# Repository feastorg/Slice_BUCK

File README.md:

# Buck Converter / Analog Signal Generator Slice

Buck Converter / Analog Signal Generator Slice for BREAD.

## Introduction

[Short introduction on the project.]

## Usage

[Explain how to use the project. Include examples and screenshots if applicable.]

## Documentation

Please refer to the [docs](/docs) for more info.

---

<div align="center">
  
</div>

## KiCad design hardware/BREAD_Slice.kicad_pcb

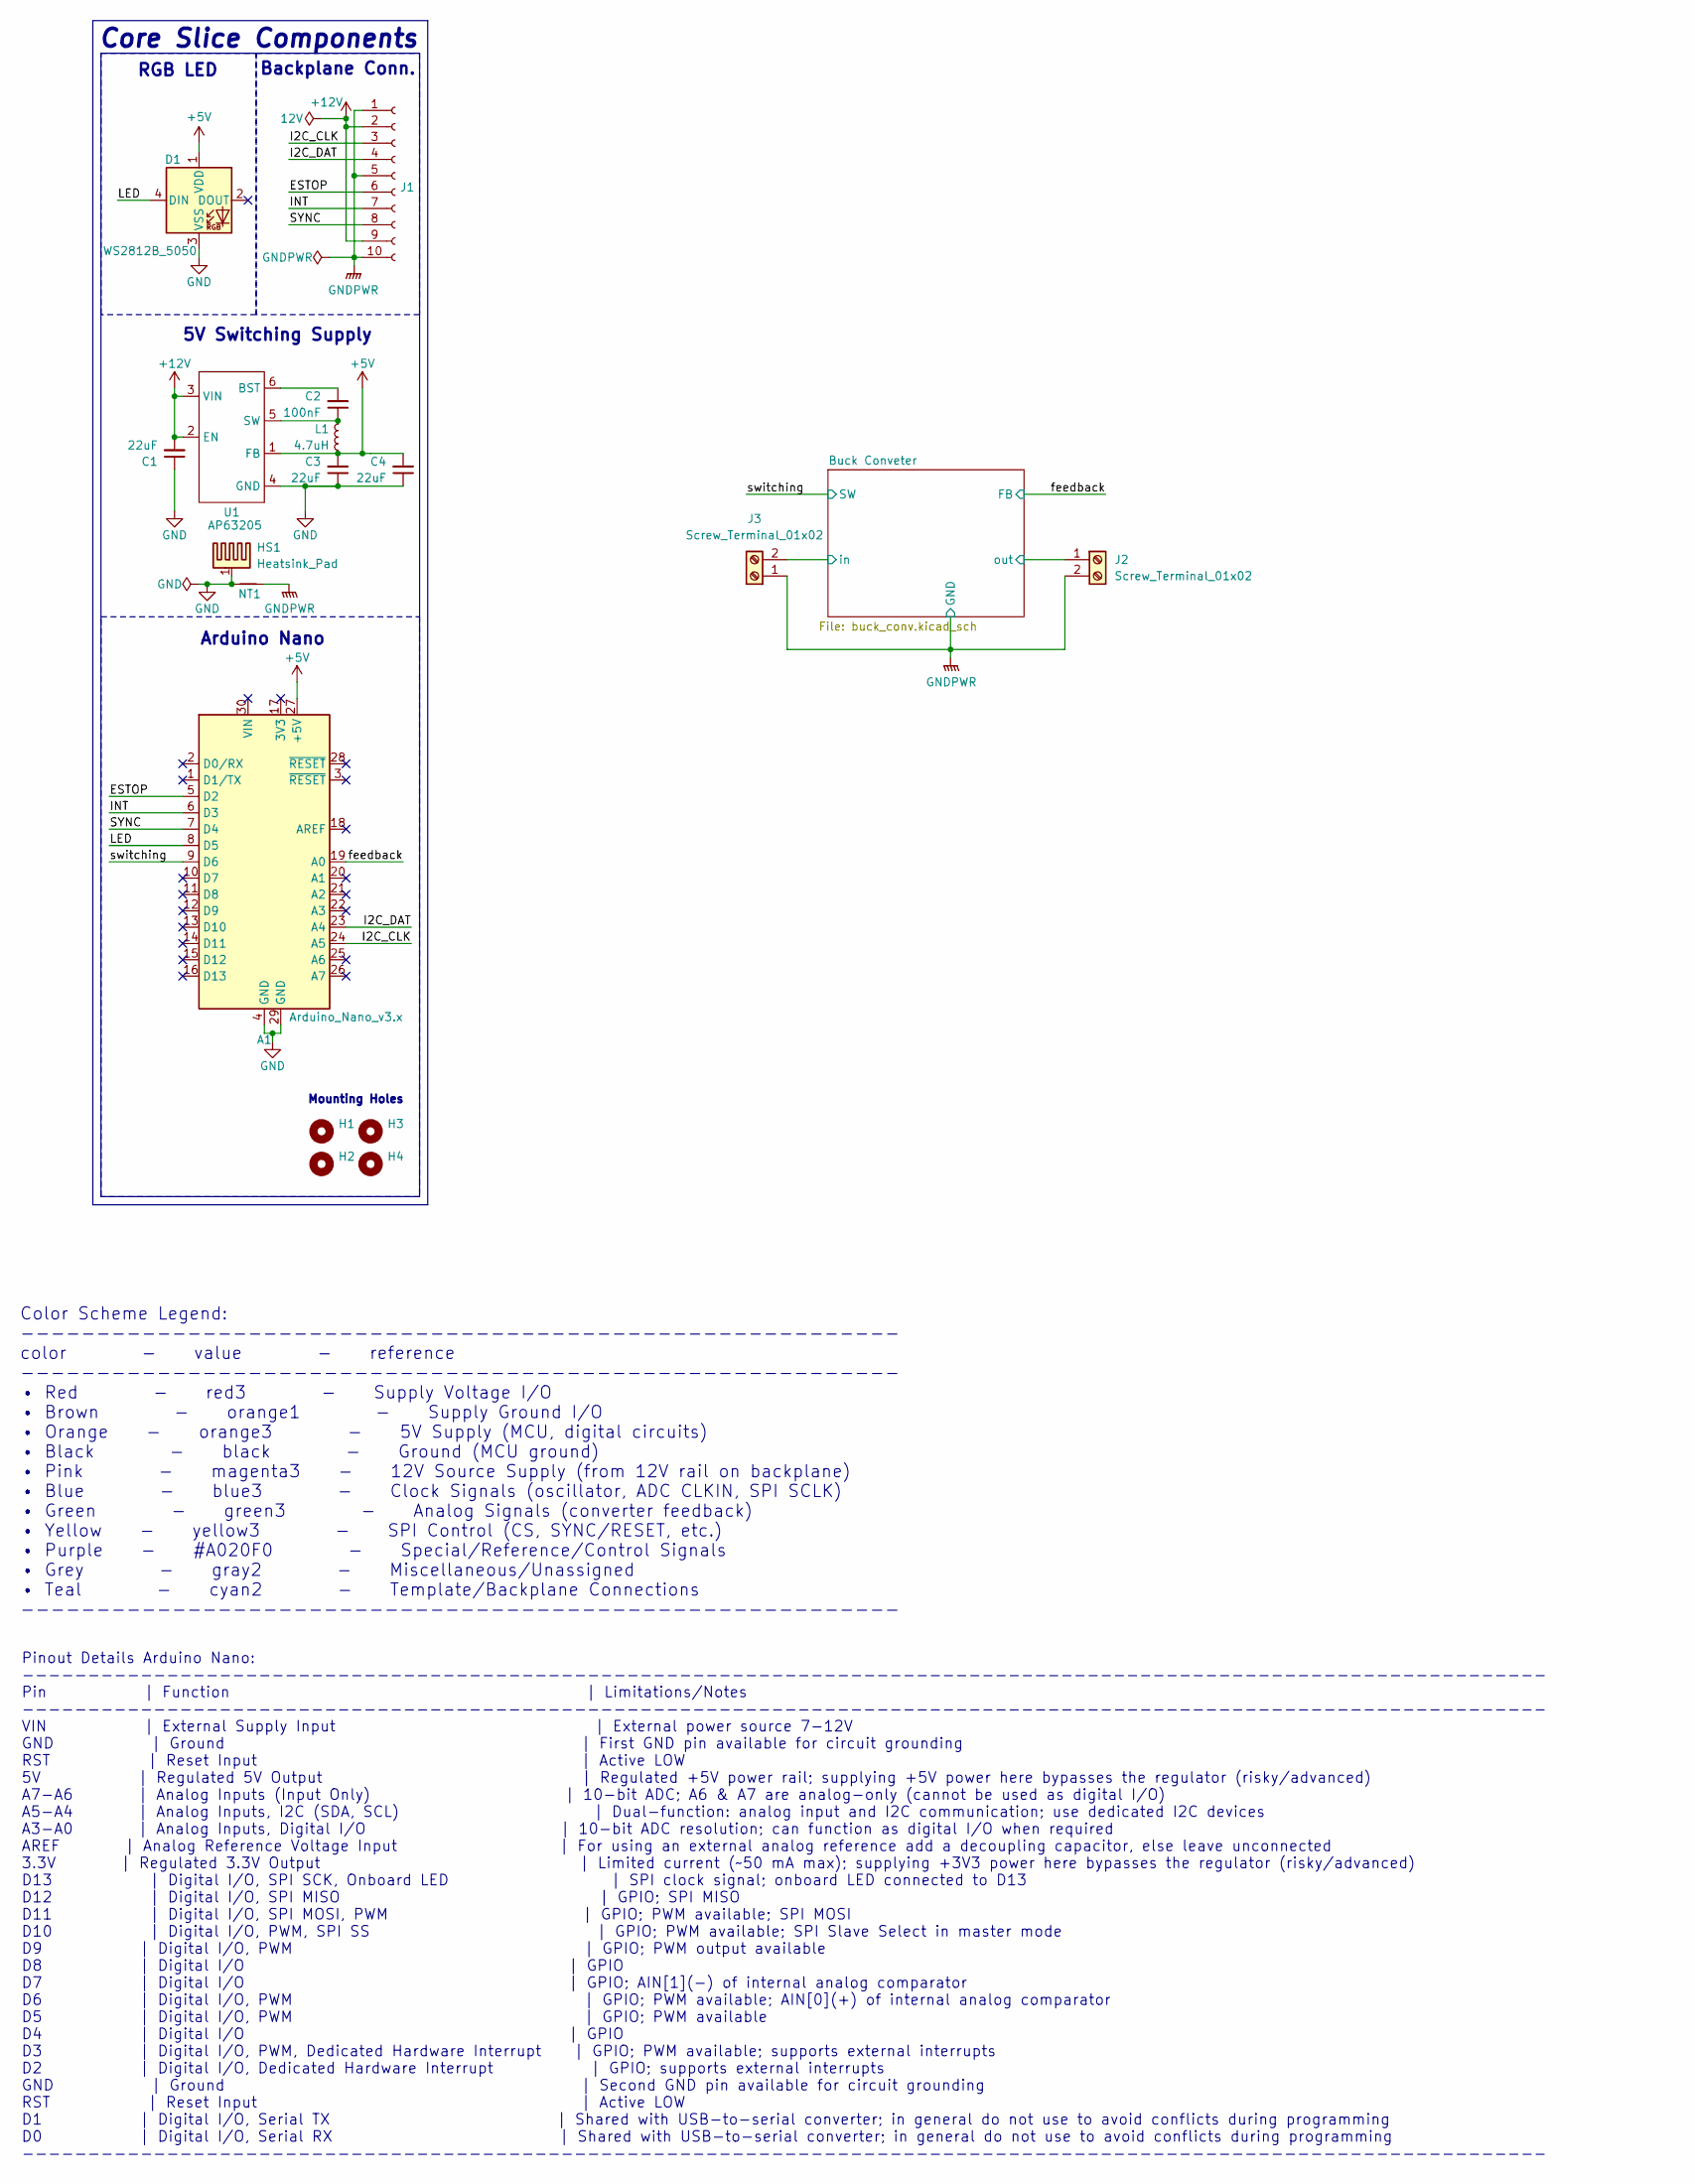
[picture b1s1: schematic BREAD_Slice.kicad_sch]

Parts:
A1: Arduino_Nano_v3.x; Arduino_Nano
C1, C3, C4: 22uF; C_1206_3216Metric
C2: 100nF; C_1206_3216Metric
D1: WS2812B_5050; WS2812-5050-4PIN
H1, H2, H3, H4: MountingHole; MountingHole_5mm
HS1: Heatsink_Pad; Thermal_Pad
J1: Conn_01x10_Female; PinSocket_1x10_P2.54mm_Horizontal
J2, J3: Screw_Terminal_01x02; TerminalBlock_4Ucon_1x02_P3.50mm_Horizontal
L1: 4.7uH; L_1210_3225Metric
NT1: NetTie_2; NetTie-2_SMD_Pad2.0mm
U1: AP63205; TSOT-23-6

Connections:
+5V: A1.27 (+5V), C3.2, C4.2, D1.1 (VDD), L1.2, U1.1 (FB)
+12V: C1.2, J1.2, J1.9, U1.2 (EN), U1.3 (VIN)
/Buck Conveter/in: J3.2; also elsewhere on the board
/Buck Conveter/out: J2.1; also elsewhere on the board
/ESTOP: A1.5 (D2), J1.6
/I2C_CLK: A1.24 (A5), J1.3
/I2C_DAT: A1.23 (A4), J1.4
/INT: A1.6 (D3), J1.7
/LED: A1.8 (D5), D1.4 (DIN)
/SYNC: A1.7 (D4), J1.8
/feedback: A1.19 (A0); also elsewhere on the board
/switching: A1.9 (D6); also elsewhere on the board
GND: A1.4 (GND), A1.29 (GND), C1.1, C3.1, C4.1, D1.3 (VSS), HS1.1, NT1.1, U1.4 (GND)
GNDPWR: J1.1, J1.5, J1.10, J2.2, J3.1, NT1.2; also elsewhere on the board
unnamed: C2.2, U1.6 (BST)
unnamed: C2.1, L1.1, U1.5 (SW)

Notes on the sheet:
5V Switching Supply
Pinout Details Arduino Nano: -------------------------------------------------------------------------------------------------------------------- Pin | Function | Limitations/Notes -------------------------------------------------------------------------------------------------------------------- V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
RGB LED
Color Scheme Legend: ---------------------------------------------------------- color - value - reference ---------------------------------------------------------- • Red - red3 - Supply Voltage I/O • Brown - orange1 - Supply Ground I/O • Orange - orange3 - 5V Supply (MCU, digital circuits) • Black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
Core Slice Components
Arduino Nano
Mounting Holes
Backplane Conn.

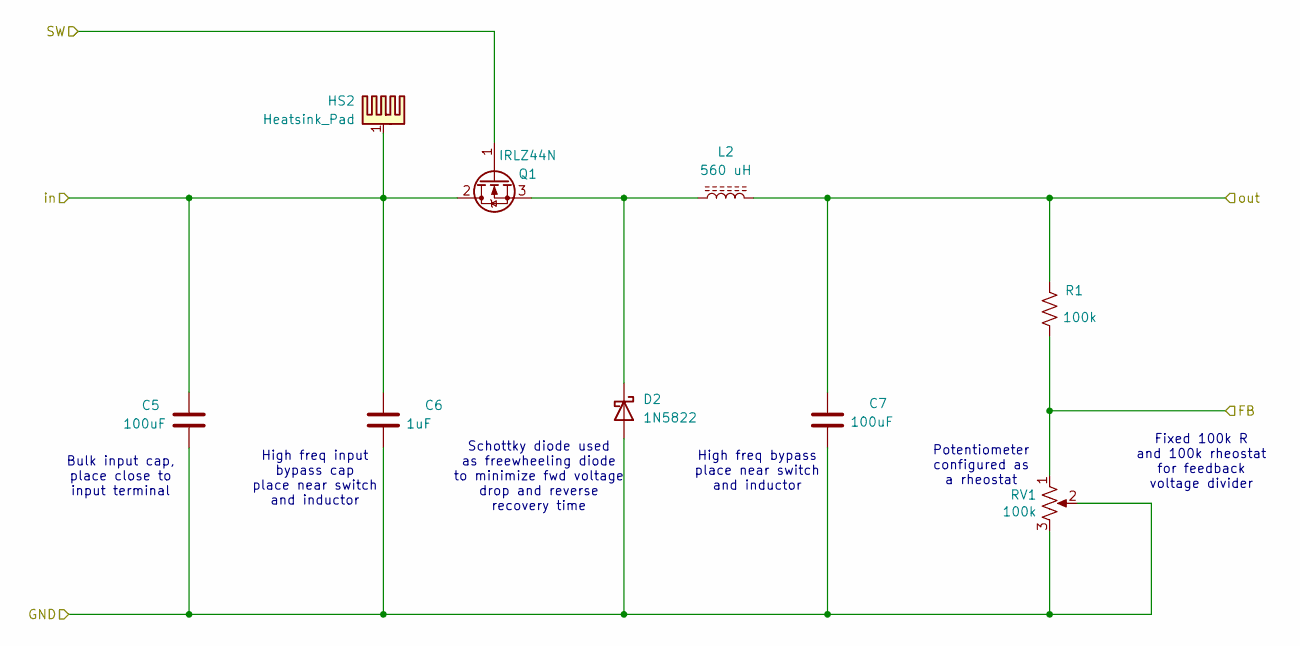
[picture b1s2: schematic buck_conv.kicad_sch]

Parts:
C5, C7: 100uF; C_Radial_D8.0mm_H11.5mm_P3.50mm
C6: 1uF; C_1206_3216Metric
D2: 1N5822; D_DO-201AD_P15.24mm_Horizontal
HS2: Heatsink_Pad; Thermal_Pad
L2: 560 uH; L_Radial_D27.9mm_P19.05mm_Vishay_IHB-3
Q1: IRLZ44N; TO-220-3_Horizontal_TabDown
R1: 100k; R_Axial_DIN0309_L9.0mm_D3.2mm_P15.24mm_Horizontal
RV1: 100k; Potentiometer_Bourns_3266W_Vertical

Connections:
/Buck Conveter/in: C5.1, C6.1, HS2.1, Q1.2 (D); also elsewhere on the board
/Buck Conveter/out: C7.1, L2.2, R1.1; also elsewhere on the board
/feedback: R1.2, RV1.1; also elsewhere on the board
/switching: Q1.1 (G); also elsewhere on the board
GNDPWR: C5.2, C6.2, C7.2, D2.2 (A), RV1.2, RV1.3; also elsewhere on the board
unnamed: D2.1 (K), L2.1, Q1.3 (S)

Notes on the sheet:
Fixed 100k R and 100k rheostat for feedback voltage divider
Schottky diode used as freewheeling diode to minimize fwd voltage drop and reverse recovery time
Bulk input cap, place close to input terminal
High freq bypass place near switch and inductor
High freq input bypass cap place near switch and inductor
Potentiometer configured as a rheostat

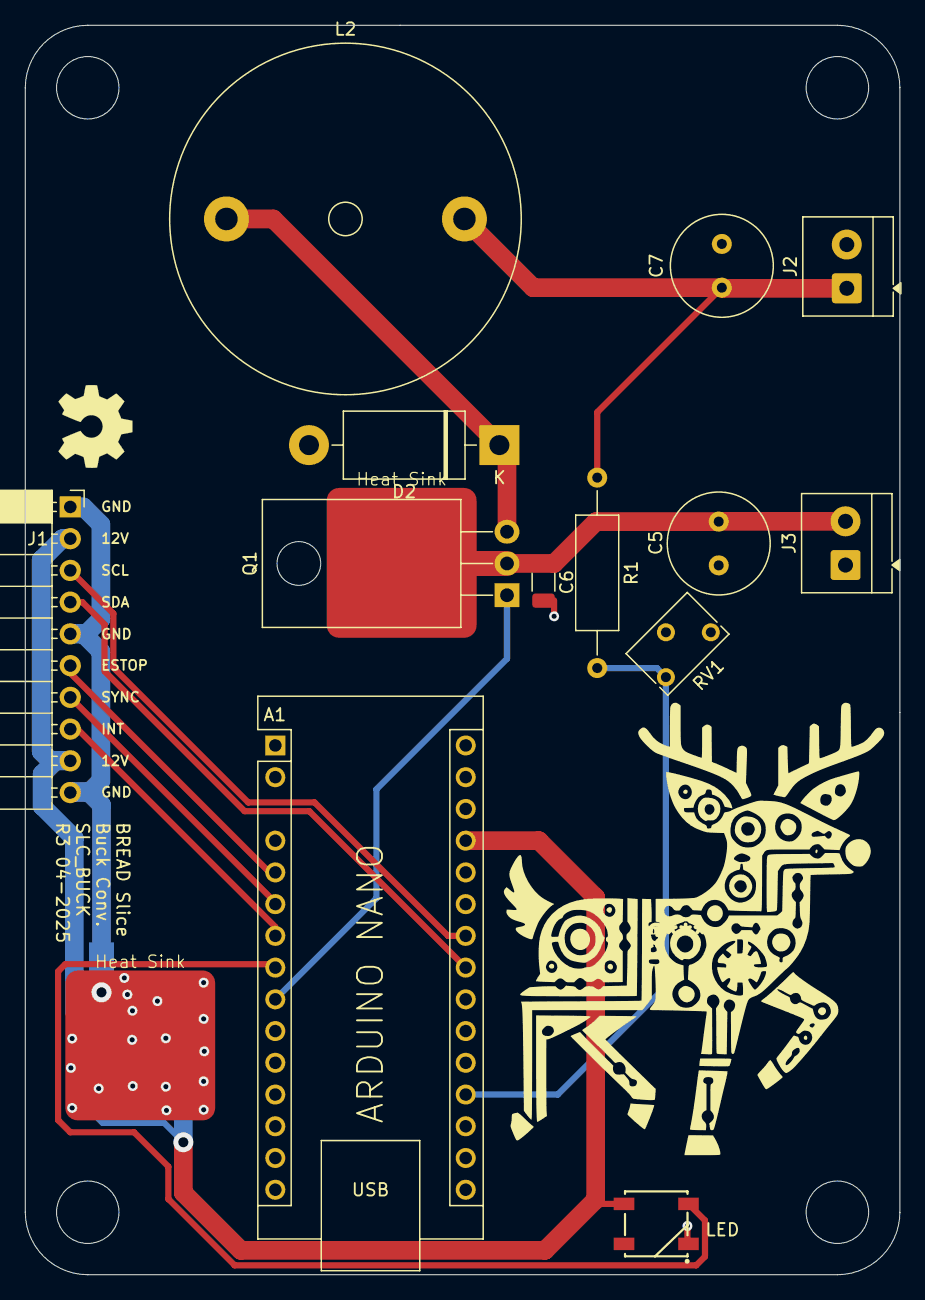
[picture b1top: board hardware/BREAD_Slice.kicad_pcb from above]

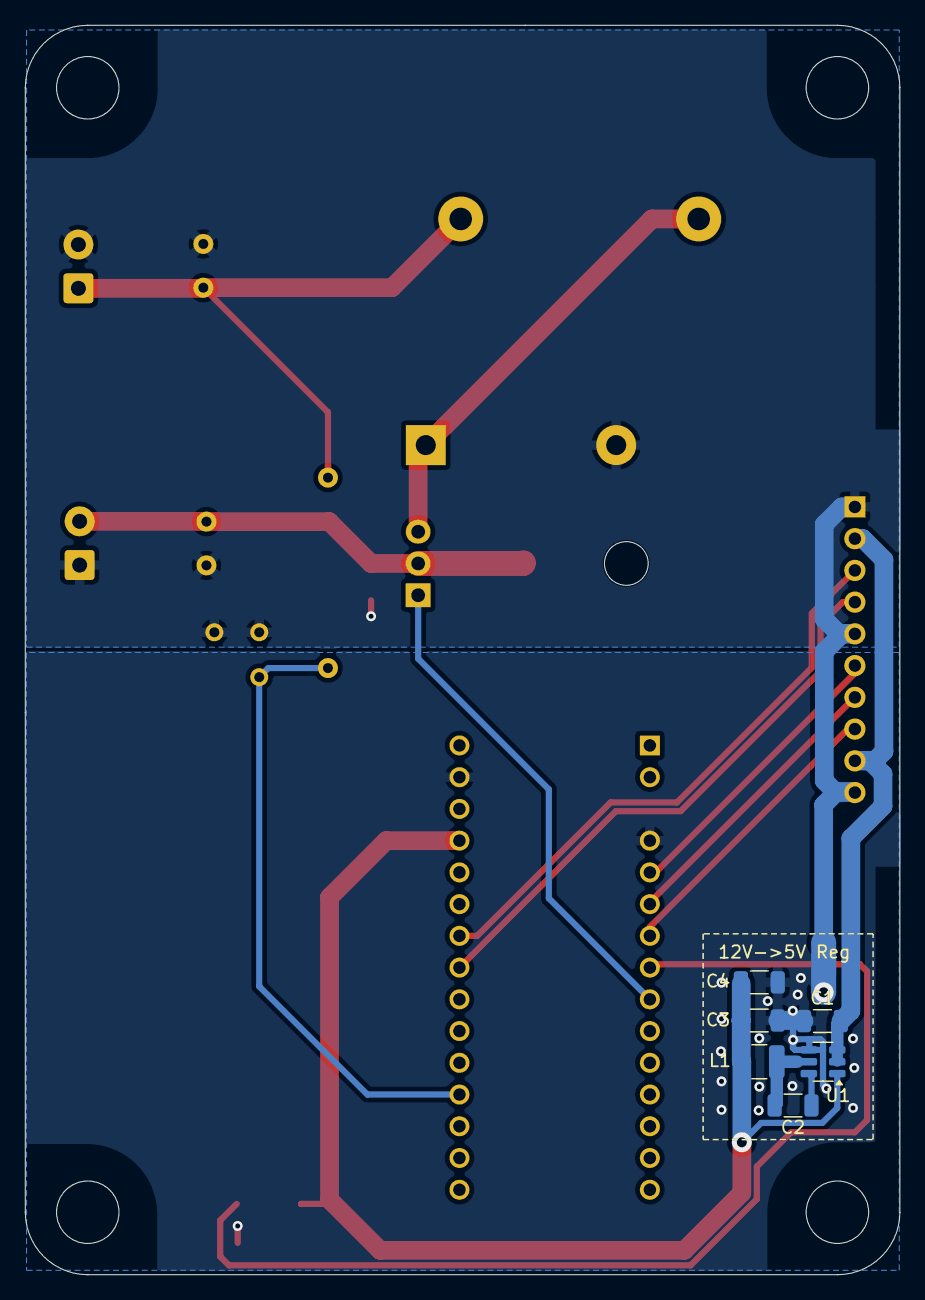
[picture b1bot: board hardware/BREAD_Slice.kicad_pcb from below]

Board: 2 copper layers, 70.0 x 100.0 mm, 27 parts (7 on the bottom side), 17 nets.

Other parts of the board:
Logo1: Logo_Open_Hardware_Small; OSHW-Symbol_6.7x6mm_SilkScreen

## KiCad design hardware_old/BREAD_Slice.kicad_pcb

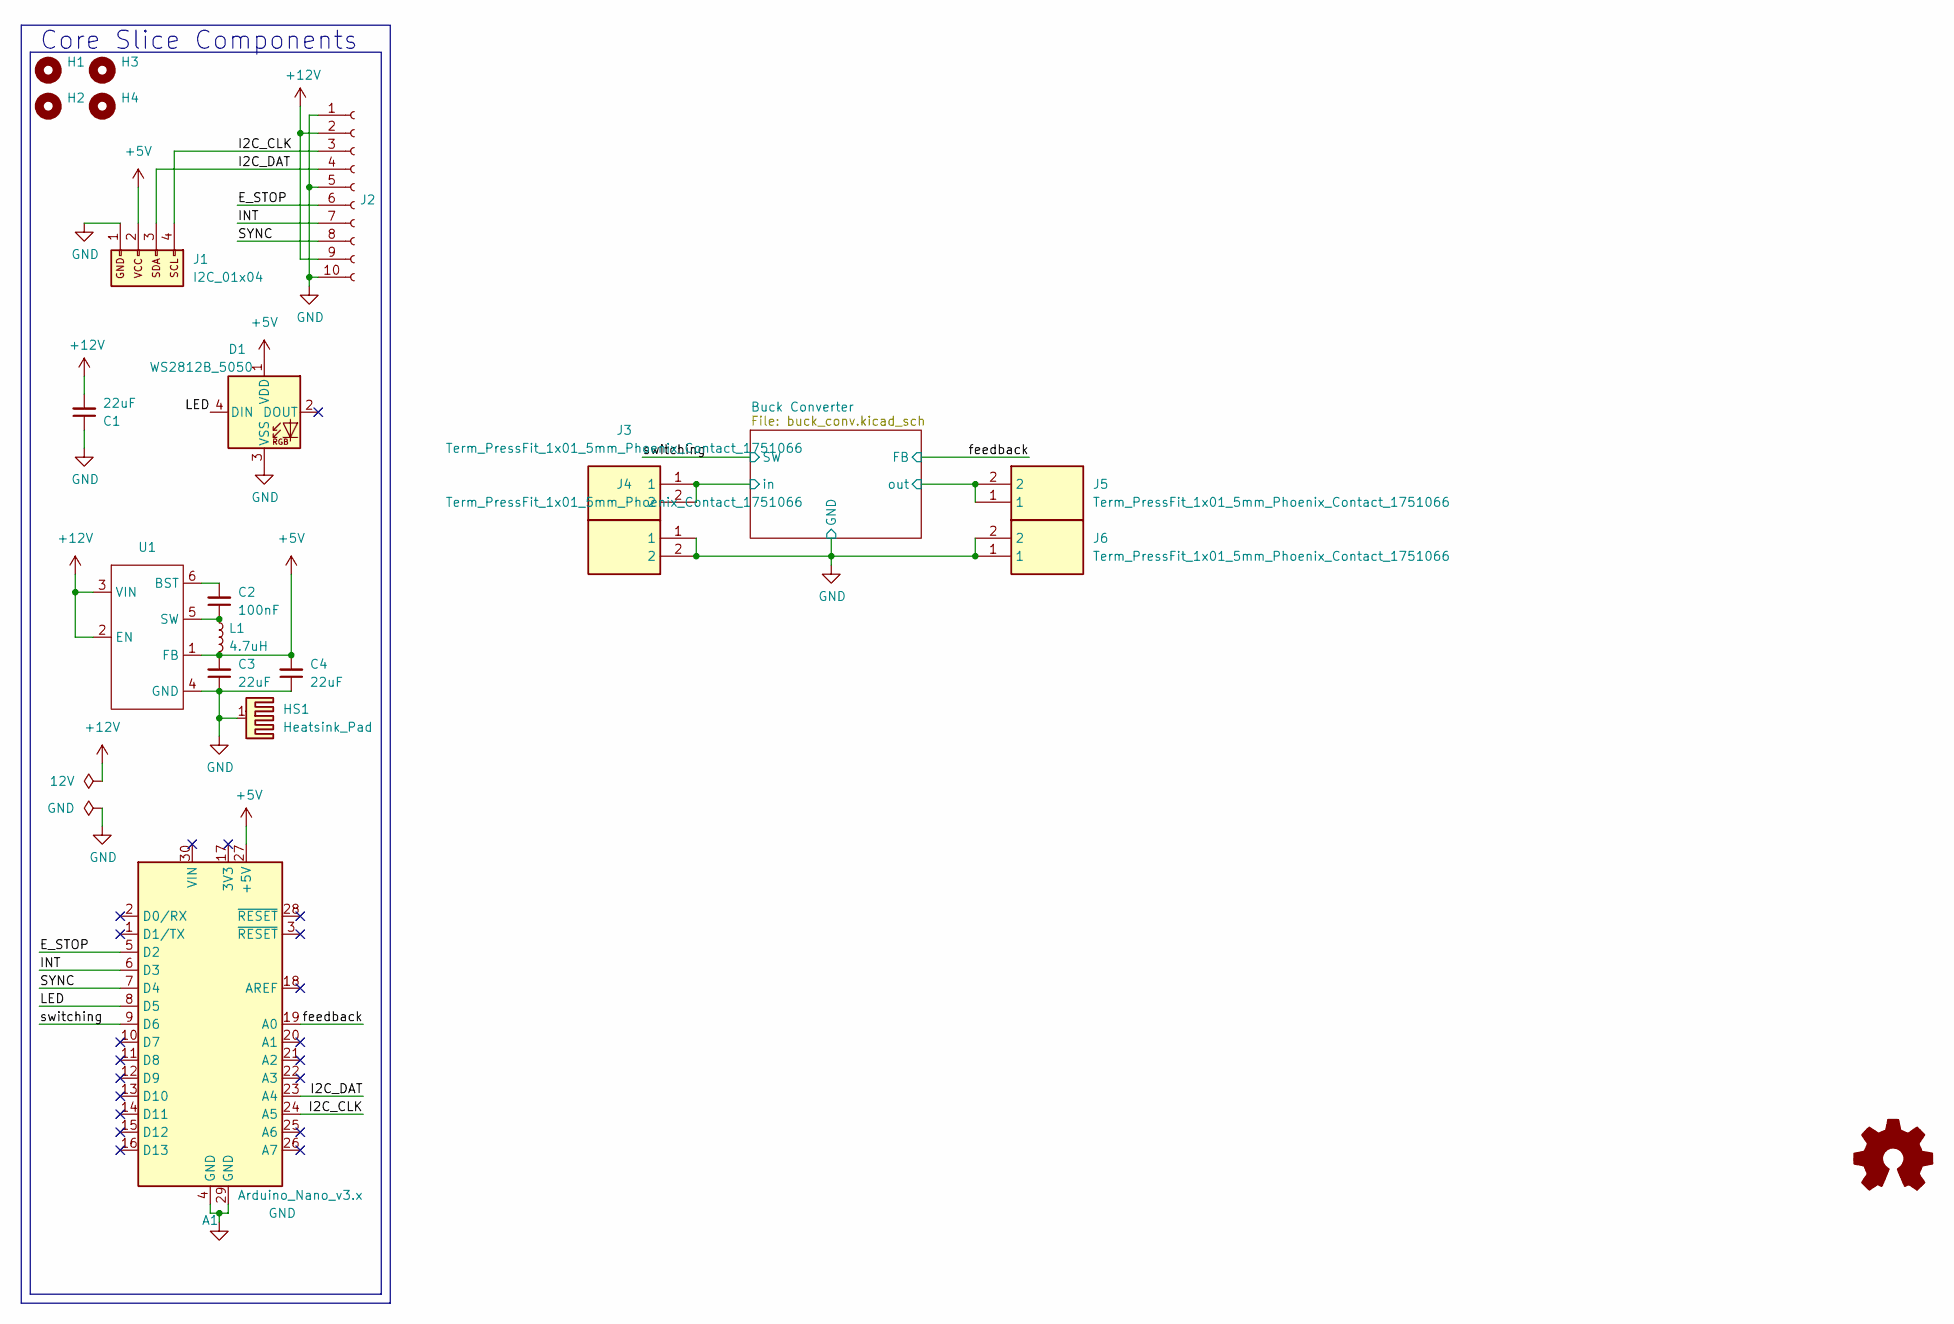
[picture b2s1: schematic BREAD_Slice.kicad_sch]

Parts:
A1: Arduino_Nano_v3.x; Arduino_Nano
C1, C3, C4: 22uF; C_1206_3216Metric
C2: 100nF; C_1206_3216Metric
D1: WS2812B_5050; WS2812-5050-4PIN
H1, H2, H3, H4: MountingHole; MountingHole_5mm
HS1: Heatsink_Pad; Thermal Pad
J1: I2C_01x04; JST_SH_SM04B-SRSS-TB_1x04-1MP_P1.00mm_Horizontal
J2: Conn_01x10_Female; PinSocket_1x10_P2.54mm_Horizontal
J3, J4, J5, J6: Term_PressFit_1x01_5mm_Phoenix_Contact_1751066; 1751066; Manufacturer_Part_Number 1751066
L1: 4.7uH; L_1210_3225Metric
U1: TSOT-23-6

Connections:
+5V: A1.27 (+5V), C3.2, C4.2, D1.1 (VDD), J1.2, L1.2, U1.1 (FB)
+12V: C1.2, J2.2, J2.9, U1.2 (EN), U1.3 (VIN)
/Buck Converter/in: J3.1, J3.2; also elsewhere on the board
/Buck Converter/out: J5.1, J5.2; also elsewhere on the board
/E_STOP: A1.5 (D2), J2.6
/I2C_CLK: A1.24 (A5), J1.4, J2.3
/I2C_DAT: A1.23 (A4), J1.3, J2.4
/INT: A1.6 (D3), J2.7
/LED: A1.8 (D5), D1.4 (DIN)
/SYNC: A1.7 (D4), J2.8
/feedback: A1.19 (A0); also elsewhere on the board
/switching: A1.9 (D6); also elsewhere on the board
GND: A1.4 (GND), A1.29 (GND), C1.1, C3.1, C4.1, D1.3 (VSS), HS1.1, J1.1, J2.1, J2.5, J2.10, J4.1, J4.2, J6.1, J6.2, U1.4 (GND); also elsewhere on the board
unnamed: C2.2, U1.6 (BST)
unnamed: C2.1, L1.1, U1.5 (SW)

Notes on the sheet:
Core Slice Components

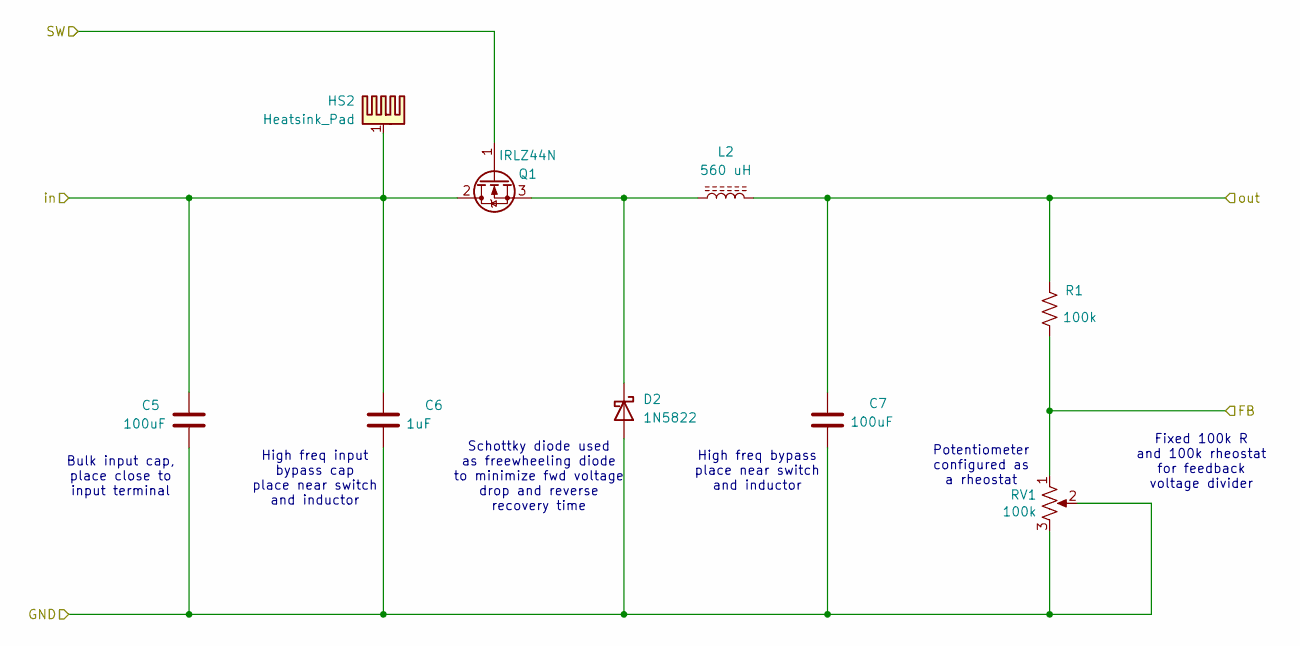
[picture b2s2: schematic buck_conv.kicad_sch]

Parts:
C5, C7: 100uF; C_Radial_D8.0mm_H11.5mm_P3.50mm
C6: 1uF; C_1206_3216Metric
D2: 1N5822; D_DO-201AD_P15.24mm_Horizontal
HS2: Heatsink_Pad; Thermal Pad
L2: 560 uH; L_Radial_D27.9mm_P19.05mm_Vishay_IHB-3
Q1: IRLZ44N; TO-220-3_Horizontal_TabDown
R1: 100k; R_Axial_DIN0309_L9.0mm_D3.2mm_P15.24mm_Horizontal
RV1: 100k; Potentiometer_Bourns_3266W_Vertical

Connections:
/Buck Converter/in: C5.1, C6.1, HS2.1, Q1.2 (D); also elsewhere on the board
/Buck Converter/out: C7.1, L2.2, R1.1; also elsewhere on the board
/feedback: R1.2, RV1.1; also elsewhere on the board
/switching: Q1.1 (G); also elsewhere on the board
GND: C5.2, C6.2, C7.2, D2.2 (A), RV1.2, RV1.3; also elsewhere on the board
unnamed: D2.1 (K), L2.1, Q1.3 (S)

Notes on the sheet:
Fixed 100k R and 100k rheostat for feedback voltage divider
Schottky diode used as freewheeling diode to minimize fwd voltage drop and reverse recovery time
Bulk input cap, place close to input terminal
High freq bypass place near switch and inductor
High freq input bypass cap place near switch and inductor
Potentiometer configured as a rheostat

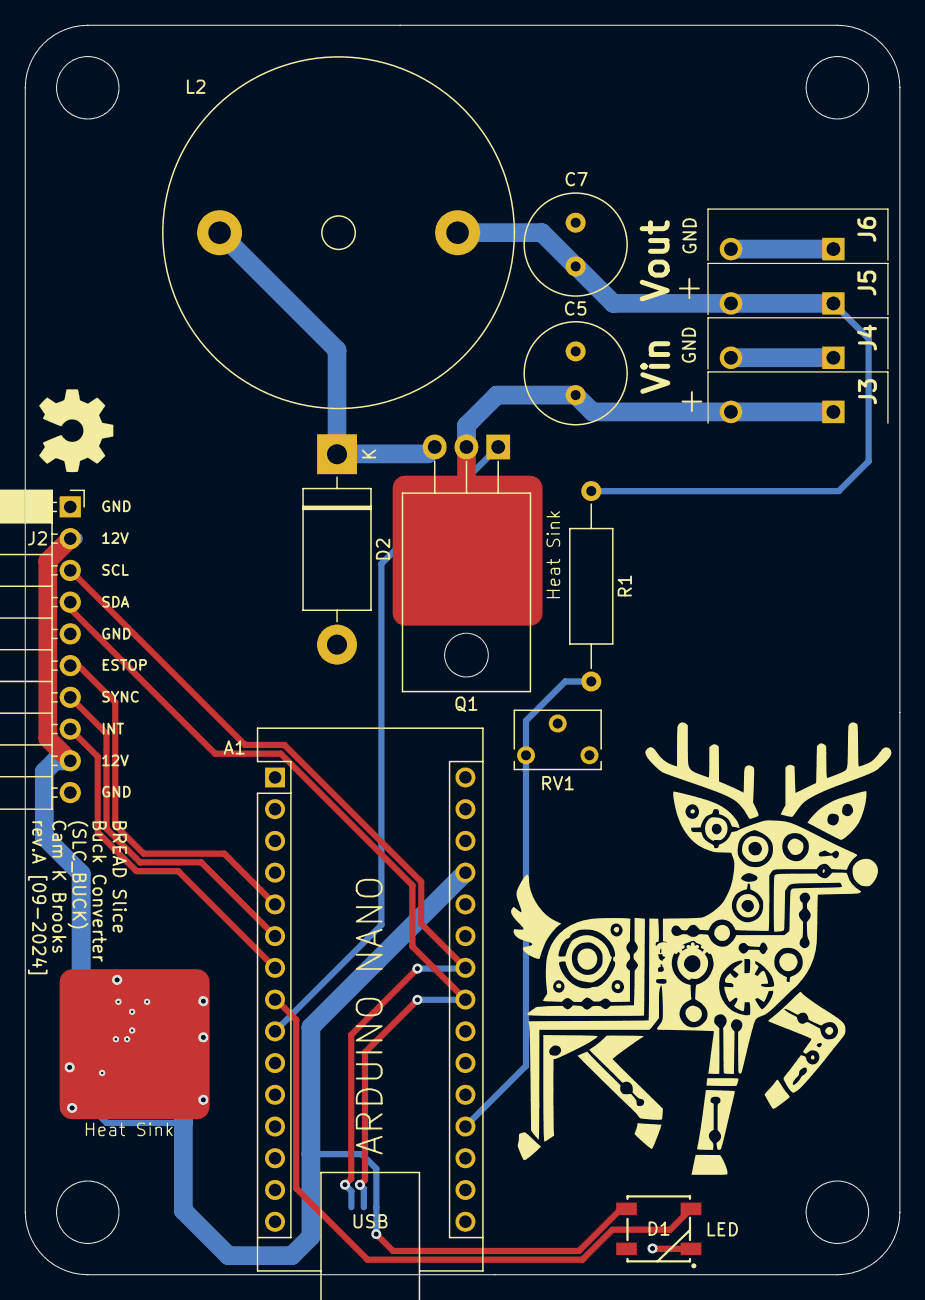
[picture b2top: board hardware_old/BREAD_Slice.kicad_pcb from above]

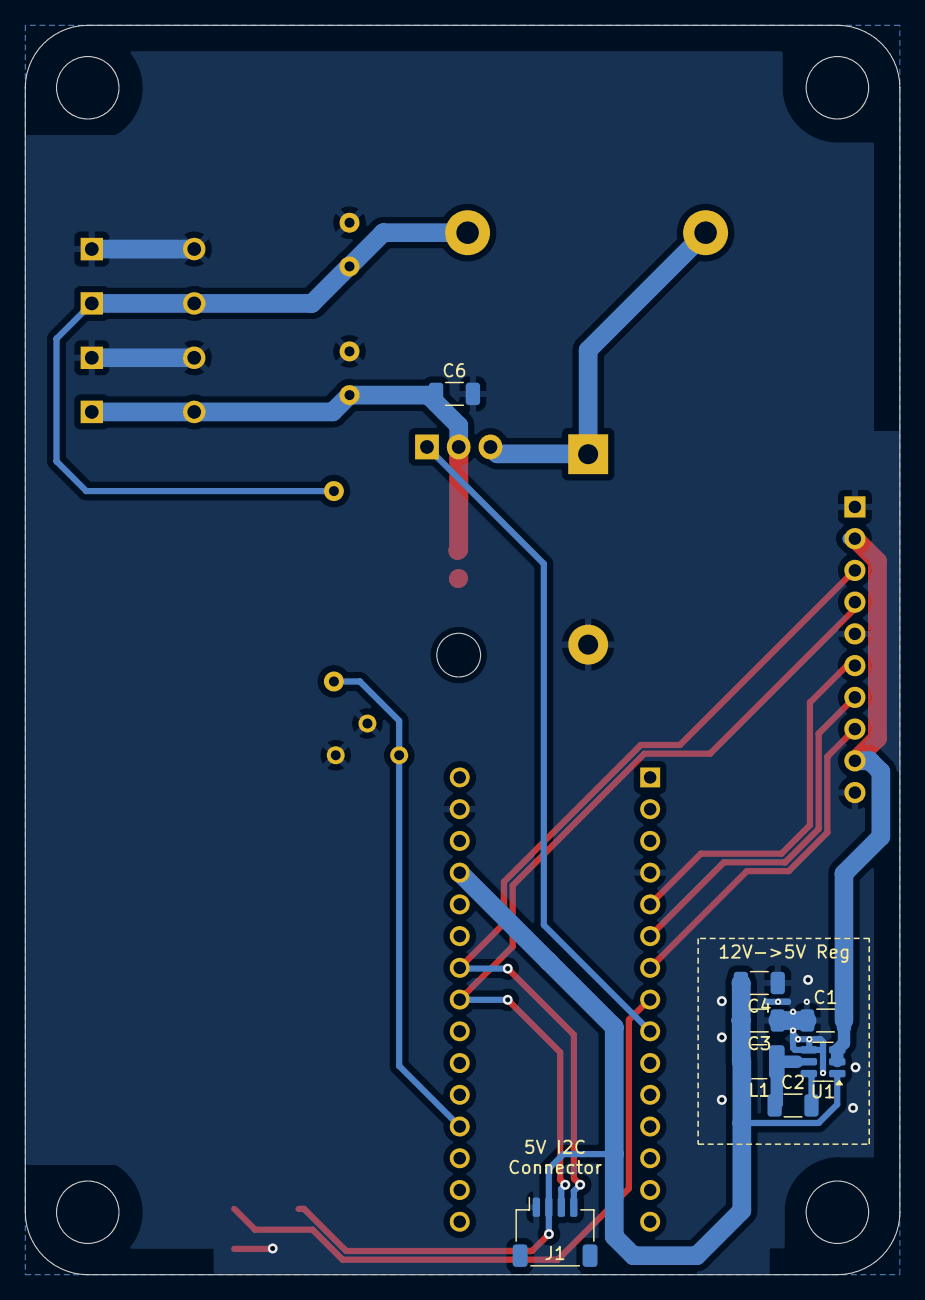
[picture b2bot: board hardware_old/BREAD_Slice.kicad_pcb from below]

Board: 2 copper layers, 70.0 x 100.0 mm, 29 parts (8 on the bottom side), 16 nets.

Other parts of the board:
Logo1: Logo_Open_Hardware_Small; OSHW-Symbol_6.7x6mm_SilkScreen

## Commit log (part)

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2024-08-16 updated to new BREAD format
2024-08-16 removed legacy hardware
2024-08-30 updated outputs for fab
2024-08-30 minor updates
2024-08-30 minor changes
2024-09-05 added art
2024-09-10 update repo
2024-09-27 cleaned up erc & drc
2024-09-30 JLCPCB order rev-A
2025-03-31 updated to use latest template
2025-03-31 removed old
2025-03-31 removed i2c conn silk
2025-04-04 finalized to 2L templ
2025-09-24 docs: add inductor part
2025-10-19 add attempt script to use current buck
2026-04-18 chore: minor updates
2026-05-20 Add slice.yaml manifest (schema v1.0)
2026-05-24 Add KiBot/docs pipeline
2026-05-24 📄 KiBot index + board renders (auto)
2026-05-24 TODO: all CI green
